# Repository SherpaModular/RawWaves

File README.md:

## Raw Waves v2

Raw Waves v2 is a sample player that functions much like a live radio. Audio sample files may be placed on a MicroSD card, and arranged into "banks" (like channels) which you may select either manually through the panel knobs, or via CV. File formats supported include RAW and WAV files.

The module is functionally identical to the popular "Raw Waves" module, and its predecessor, "Radio Music" by Tom Whitwell of Music Thing Modular. These previous modules are no longer available, having been built upon the now-discontinued Teensy 3 microcontroller.

Raw Waves v2 has been completely redesigned to use the Teensy 4 platform. Because the module uses the Teensy 4 microcontroller, the "Raw Waves v2" will not be compatible with other alternative firmware made for Radio Music (e.g. 'Chord Organ').

Raw Waves v2 still supports all of the settings in the SETTINGS.TXT file that you came to know and love in the earlier models. If you haven't played with the settings, you really should!

#### Specifications
Audio output: 16-bit audio output, with hardware anti-alias filtering.
Dimensions: 4 hp, 21mm deep.
Power specifications: Requires +12v (at 100 mA) and -12v (at 10 mA). The module features several protections against accidental reverse power connection: First, a keyed 10-pin Eurorack standard connector, second, automatically resetting fuses, and thirdly, protection diodes.
CV Inputs are designed for 0-5v, with reasonable over/undervoltage protection built-in.

#### Compiling the code
My preference is to use Visual Studio Code:
1. Install the Microsoft "Arduino for Visual Studio Code" extension
2. Add the Teensy packages. You can accomplish this in the "Arduino for Visual Studio Code" extension settings by adding the URL https://www.pjrc.com/teensy/package_teensy_index.json to the "Arduino: Additional Urls, Additional URLs for 3rd party packages." setting.
3. The following file contents, placed into the repo under the filename .vscode\arduino.json helps with other details:
```
{
    "sketch": "Software\\RawWavesV2\\RawWavesV2.ino",
    "configuration": "usb=serial,speed=600,opt=o2std,keys=en-us",
    "board": "teensy:avr:teensy40",
    "output": "ArduinoOutput\\RawWavesV2",
    "port": "COM3"
}
```
4. In VS Code, activate the Command Palette (typically by pressing F1), and choose "Ardunio: Verify".
5. If all codes well, the compiled output should appear in the repo directory, under ArduinoOutput\RawWavesV2

#### License  
Raw Waves is Open Hardware. It is a derivate work of ["Radio Music", by Tom Whitwell](https://github.com/TomWhitwell/RadioMusic). 
All hardware and software design in this project is Creative Commons licensed by Jim Mulvey: [CC-BY-SA: Attribution / ShareAlike](https://creativecommons.org/licenses/by-sa/3.0/)
If you use any work in this project, you should credit Tom Whitwell and me, and you must republish any changes you make under the same license.
This license does permit commercial use of these designs, but consider getting in touch before selling anything.
This project includes work from the [Teensy](https://www.pjrc.com/teensy/) project, which is not covered by this license.

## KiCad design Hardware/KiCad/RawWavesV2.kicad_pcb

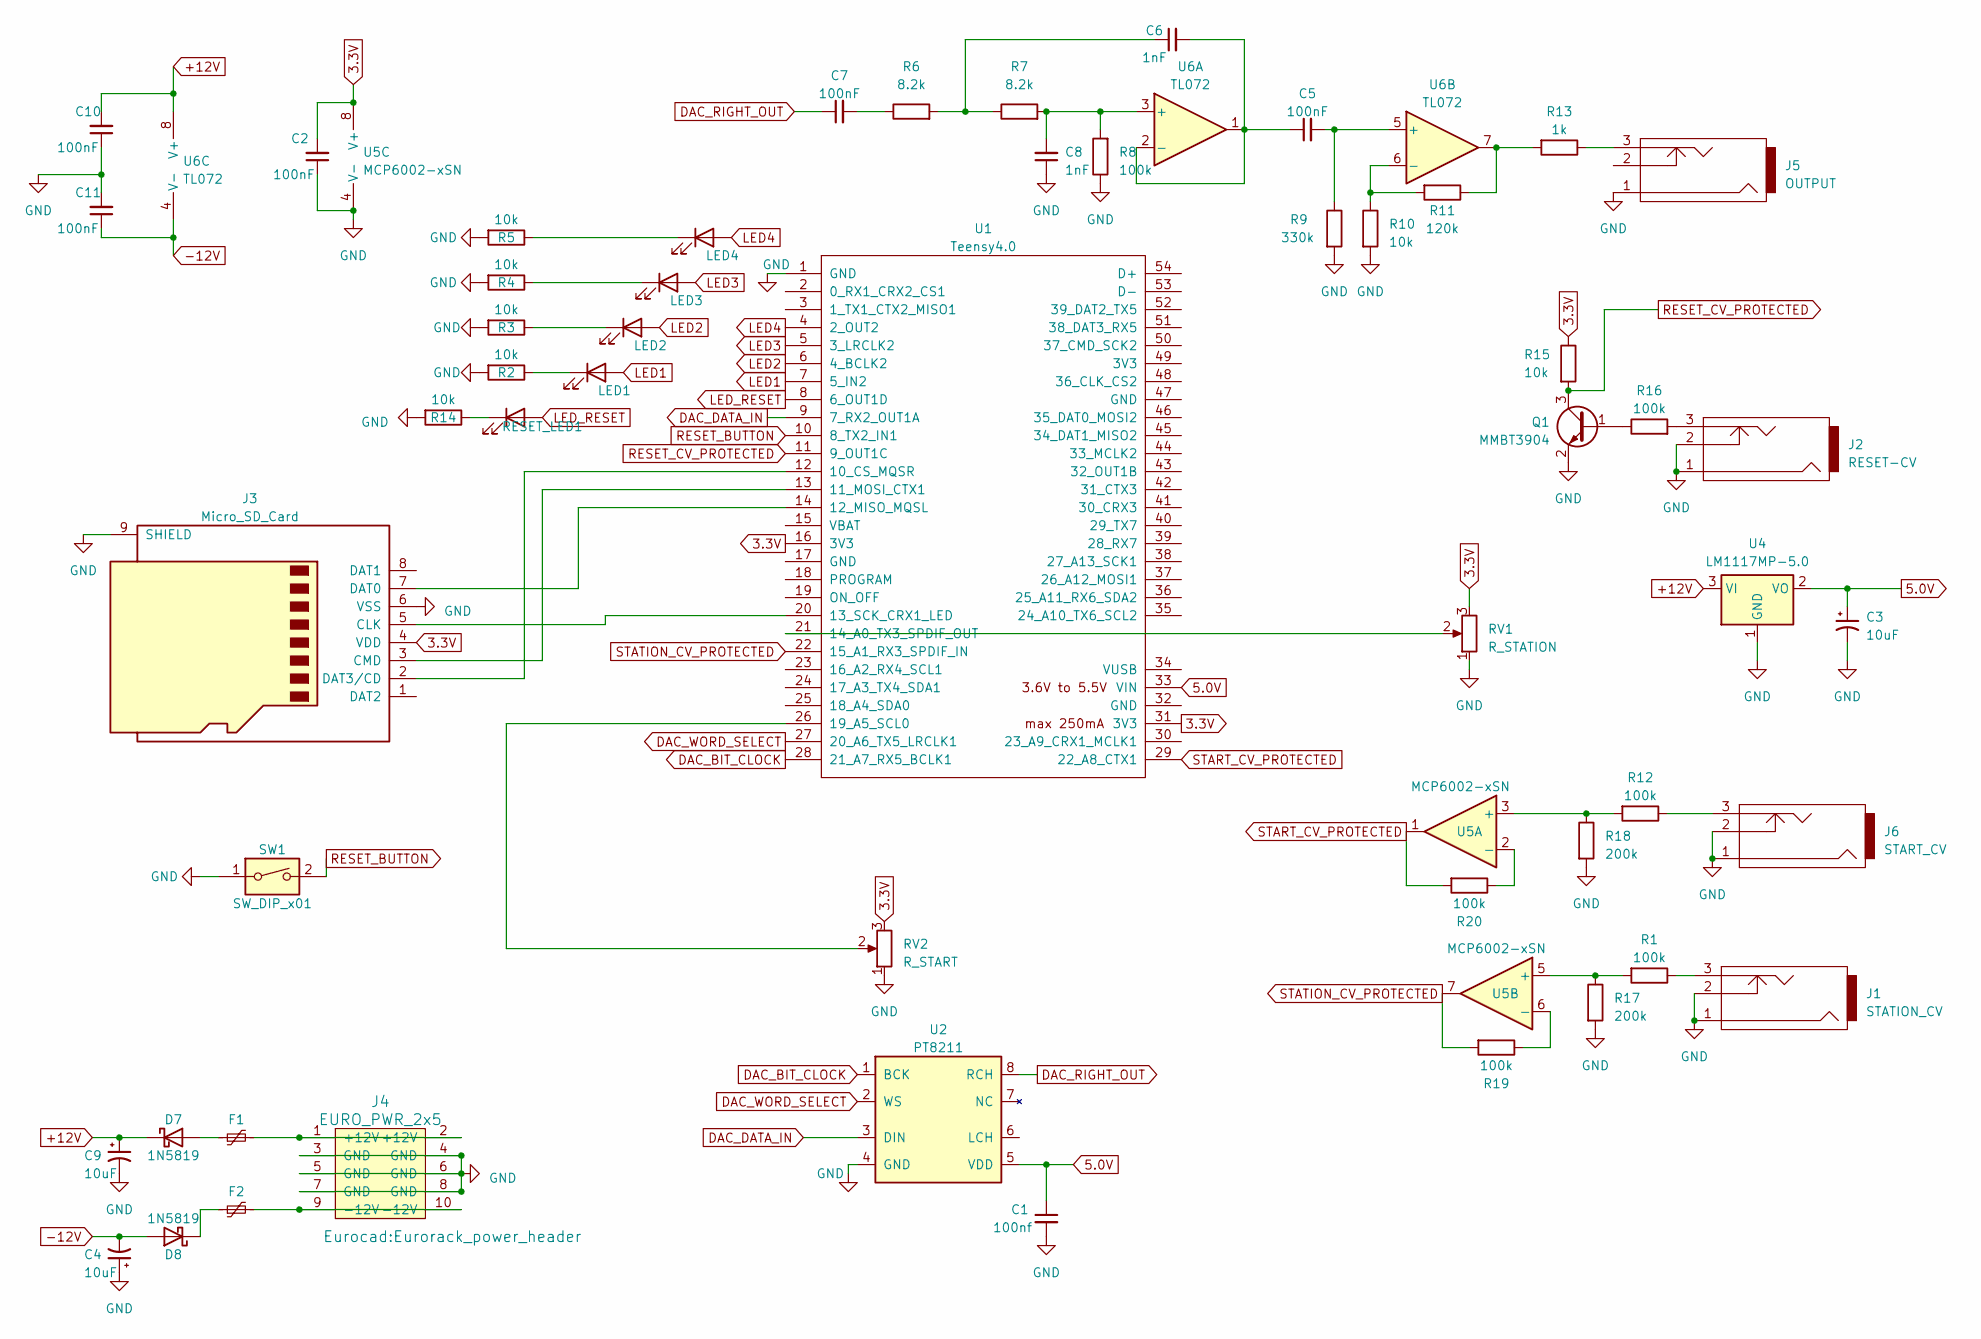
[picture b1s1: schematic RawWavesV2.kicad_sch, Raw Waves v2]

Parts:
C1: 100nf; C_0603_1608Metric
C2, C5, C7, C10, C11: 100nF; C_0603_1608Metric
C3, C4, C9: 10uF; CP_Elec_4x5.4
C6, C8: 1nF; C_0603_1608Metric
D7, D8: 1N5819; D_SOD-323
F1, F2: Polyfuse_Small; R_0805_2012Metric
J1: STATION_CV; PJ301M-12_Compact
J2: RESET-CV; PJ301M-12_Compact
J3: Micro_SD_Card; YAMAICHI_MICROSD_VERTICAL
J4: EURO_PWR_2x5; Eurorack_power_header
J5: OUTPUT; PJ301M-12_Compact
J6: START_CV; PJ301M-12_Compact
LED1: LED1; LED_D3.0mm
LED2: LED2; LED_D3.0mm
LED3: LED3; LED_D3.0mm
LED4: LED4; LED_D3.0mm
Q1: MMBT3904; SOT-23
R1, R8, R12, R16, R19, R20: 100k; R_0603_1608Metric
R2, R3, R4, R5, R10, R14, R15: 10k; R_0603_1608Metric
R6, R7: 8.2k; R_0603_1608Metric
R9: 330k; R_0603_1608Metric
R11: 120k; R_0603_1608Metric
R13: 1k; R_0603_1608Metric
R17, R18: 200k; R_0603_1608Metric
RESET_LED1: RESET_LED; LED_D3.0mm
RV1: R_STATION; Alpha9mmPot
RV2: R_START; Alpha9mmPot
SW1: SW_DIP_x01; Push_E-Switch_KS01Q01
U1: Teensy4.0; Teensy4.0-RawWavesV2
U2: PT8211; SOIC-8_3.9x4.9mm_P1.27mm
U4: LM1117MP-5.0; SOT-223-3_TabPin2
U5: MCP6002-xSN; SOIC-8_3.9x4.9mm_P1.27mm
U6: TL072; SOIC-8_3.9x4.9mm_P1.27mm

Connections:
3.3V: C2.2, J3.4 (VDD), R15.1, RV1.3, RV2.3, U1.16 (3V3), U1.31 (3V3), U5.8 (V+)
5.0V: C1.1, C3.1, U1.33 (VIN), U2.5 (VDD), U4.2 (VO)
+12V: C9.1, C10.2, D7.1 (K), U4.3 (VI), U6.8 (V+)
-12V: C4.2, C11.1, D8.2 (A), U6.4 (V-)
DAC_BIT_CLOCK: U1.28 (21_A7_RX5_BCLK1), U2.1 (BCK)
DAC_DATA_IN: U1.9 (7_RX2_OUT1A), U2.3 (DIN)
DAC_RIGHT_OUT: C7.1, U2.8 (RCH)
DAC_WORD_SELECT: U1.27 (20_A6_TX5_LRCLK1), U2.2 (WS)
GND: C1.2, C2.1, C3.2, C4.1, C8.1, C9.2, C10.1, C11.2, J1.1, J1.2, J2.1, J2.2, J3.6 (VSS), J3.9 (SHIELD), J4.3 (GND), J4.4 (GND), J4.5 (GND), J4.6 (GND), J4.7 (GND), J4.8 (GND), J5.1, J6.1, J6.2, Q1.2 (E), R2.2, R3.2, R4.2, R5.2, R8.1, R9.2, R10.2, R14.2, R17.2, R18.2, RV1.1, RV2.1, SW1.1, U1.1 (GND), U2.4 (GND), U4.1 (GND), U5.4 (V-)
LED1: LED1.2 (A), U1.7 (5_IN2)
LED2: LED2.2 (A), U1.6 (4_BCLK2)
LED3: LED3.2 (A), U1.5 (3_LRCLK2)
LED4: LED4.2 (A), U1.4 (2_OUT2)
LED_RESET: RESET_LED1.2 (A), U1.8 (6_OUT1D)
unnamed: C6.1, R6.2, R7.1
unnamed: C7.2, R6.1
unnamed: D7.2 (A), F1.1
unnamed: D8.1 (K), F2.1
unnamed: F1.2, J4.1 (+12V), J4.2 (+12V)
unnamed: F2.2, J4.9 (-12V), J4.10 (-12V)
unnamed: J1.3, R1.1
unnamed: J2.3, R16.2
unnamed: J3.5 (CLK), U1.20 (13_SCK_CRX1_LED)
unnamed: J3.3 (CMD), U1.13 (11_MOSI_CTX1)
unnamed: J3.7 (DAT0), U1.14 (12_MISO_MQSL)
unnamed: J3.2 (DAT3/CD), U1.12 (10_CS_MQSR)
unnamed: J5.3, R13.1
unnamed: J6.3, R12.1
unnamed: LED1.1 (K), R2.1
unnamed: LED2.1 (K), R3.1
unnamed: LED3.1 (K), R4.1
unnamed: LED4.1 (K), R5.1
unnamed: Q1.1 (B), R16.1
unnamed: R11.1, R13.2, U6.7
unnamed: R14.1, RESET_LED1.1 (K)
unnamed: RV1.2, U1.21 (14_A0_TX3_SPDIF_OUT)
unnamed: RV2.2, U1.26 (19_A5_SCL0)
unnamed: R12.2, R18.1, U5.3 (+)
unnamed: R20.1, U5.2 (-)
unnamed: R1.2, R17.1, U5.5 (+)
unnamed: R19.1, U5.6 (-)
unnamed: C8.2, R7.2, R8.2, U6.3 (+)
unnamed: C5.1, C6.2, U6.1, U6.2 (-)
unnamed: C5.2, R9.1, U6.5 (+)
unnamed: R10.1, R11.2, U6.6 (-)
RESET_BUTTON: SW1.2, U1.10 (8_TX2_IN1)
RESET_CV_PROTECTED: Q1.3 (C), R15.2, U1.11 (9_OUT1C)
START_CV_PROTECTED: R20.2, U1.29 (22_A8_CTX1), U5.1
STATION_CV_PROTECTED: R19.2, U1.22 (15_A1_RX3_SPDIF_IN), U5.7

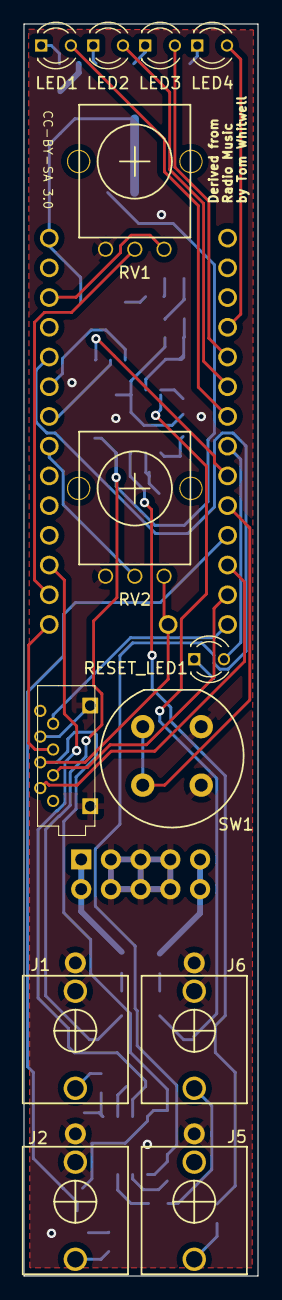
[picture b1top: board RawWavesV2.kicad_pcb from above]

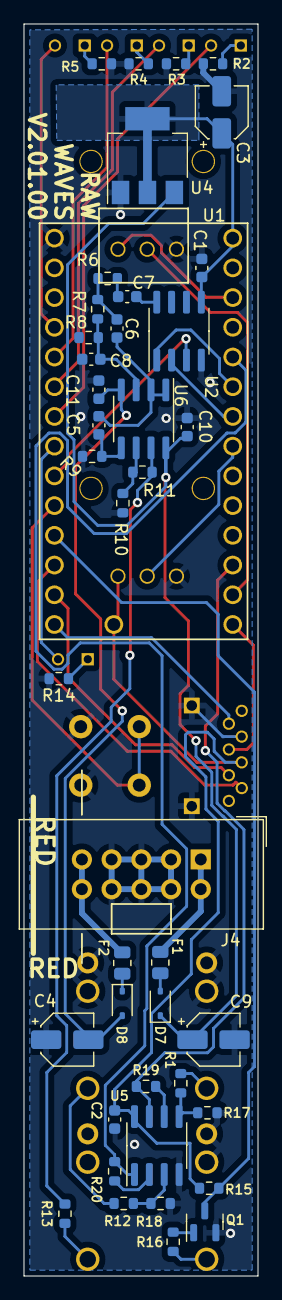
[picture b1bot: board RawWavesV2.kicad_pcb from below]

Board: 2 copper layers, 20.0 x 107.0 mm, 55 parts (42 on the bottom side), 49 nets.

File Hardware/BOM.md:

| Designator                     | Footprint                 | Quantity | Value               |
| ------------------------------ | ------------------------- | -------- | ------------------- |
| RV1                            | Alpha9mmPot               | 1        | B50k                |
| LED1,LED2,LED3,LED4,RESET_LED1 | LED_D3.0mm                | 5        | 3mm LED, high lumen |
| J3                             | YAMAICHI_MICROSD_VERTICAL | 1        | Micro_SD_Card       |
| J1,J2,J5,J6                    | PJ301M-12_Compact         | 4        | Thonkiconn          |
| SW1                            | Push_E-Switch_KS01Q01     | 1        | SW_DIP_x01          |
| RV2                            | Alpha9mmPot               | 1        | B50k                |
| R2,R3,R4,R5,R10,R14,R15        | R_0603_1608Metric         | 7        | 10k, 1%             |
| C3,C9,C4                       | CP_Elec_4x5.4             | 3        | 10uF, 25v           |
| C1,C11,C2,C10,C7,C5            | C_0603_1608Metric         | 6        | 100nF, 25v          |
| R16,R19,R8,R12,R1,R20          | R_0603_1608Metric         | 6        | 100k, 1%            |
| R17,R18                        | R_0603_1608Metric         | 2        | 200k, 1%            |
| D8,D7                          | D_SOD-323                 | 2        | 1N5819              |
| U1                             | Teensy4.0                 | 1        | Teensy4.0           |
| R13                            | R_0603_1608Metric         | 1        | 1k, 1%              |
| F2,F1                          | R_0805_2012Metric         | 2        | Polyfuse_Small      |
| U2                             | SOIC-8_3.9x4.9mm_P1.27mm  | 1        | PT8211              |
| R11                            | R_0603_1608Metric         | 1        | 120k, 1%            |
| U5                             | SOIC-8_3.9x4.9mm_P1.27mm  | 1        | MCP6002             |
| R7,R6                          | R_0603_1608Metric         | 2        | 5.6k, 1%            |
| U4                             | SOT-223-3_TabPin2         | 1        | LM1117MP-5.0        |
| Q1                             | SOT-23                    | 1        | MMBT3904            |
| U6                             | SOIC-8_3.9x4.9mm_P1.27mm  | 1        | TL072               |
| C8,C6                          | C_0603_1608Metric         | 2        | 1nF, 25v            |
| R9                             | R_0603_1608Metric         | 1        | 330k, 1%            |
| J4                             | Eurorack_power_header     | 1        | EURO_PWR_2x5        |

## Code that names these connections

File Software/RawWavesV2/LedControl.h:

#ifndef LedControl_h
#define LedControl_h

/**
 * Raw Waves LED control
 *
 * 4 LEDs across the top and 1 reset LED.
 *
 */
#define LED0 2 // was 6 before PCB change
#define LED1 3 // was 5 before PCB change
#define LED2 4
#define LED3 5 // was 3 before PCB change
#define RESET_LED 6 // Reset LED indicator. Was 11 in Teensy 3.2 but conflicts with the SD card in Teensy 4 // was 2 before PCB change

class LedControl {

	public:
		void init();
		void single(int index);
		void multi(uint8_t bits);
		void showReset(boolean high);

};
#endif

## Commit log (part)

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2021-02-24 Add Voltage Supervisor
2021-02-24 Widen Pogo Hole
    Replaced "Pogo 1.6/0.8" with "Pogo 1.6/0.9"
2023-07-02 Remove old v1 files
2023-07-16 Add final v2 schematic, PCB, BOM and software
2023-07-16 Add README with license
2023-07-17 Add compile instructions; ino file must match parent folder
2025-05-16 'Button' does not name a type
    Intended to fix #6

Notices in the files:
Hardware/KiCad/RawWavesV2.kicad_pcb:
CC-BY-SA 3.0
